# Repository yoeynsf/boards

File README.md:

# boards
A collection of the various boards that I make sometimes.

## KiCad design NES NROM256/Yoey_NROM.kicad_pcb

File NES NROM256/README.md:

# NES NROM-256
An open-source NES NROM cartridge PCB.

## License
This is licensed under the [TAPR Open Hardware License](www.tapr.org/OHL)

## Special Thanks 
- [@Trirosmos](https://github.com/Trirosmos)
- [@Lockster-inc](https://github.com/Lockster-Inc)

For advice and help!

- [@Persune](https://github.com/Gumball2415)

For supplying the cartridge pin footprint!

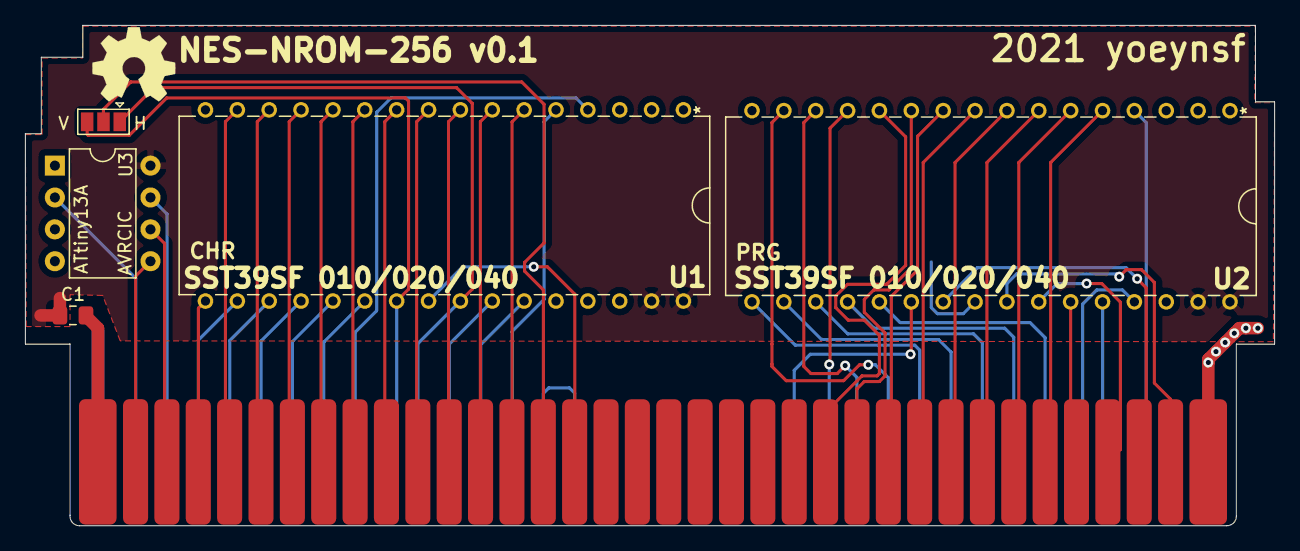
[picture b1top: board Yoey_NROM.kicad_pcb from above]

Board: 2 copper layers, 99.6 x 39.9 mm, 6 parts (0 on the bottom side), 55 nets.

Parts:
C1: 0.1µF; C_0805_2012Metric_Pad1.18x1.45mm_HandSolder
J1: Cart Connector; NES-CONN
JP1: V / H; SolderJumper-3_P1.3mm_Open_Pad1.0x1.5mm
U1: SST39SF 010/020/040; SST39SF040-70-4C-PHE
U2: SST39SF040; SST39SF040-70-4C-PHE
U3: CIC; DIP-8_W7.62mm

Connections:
CIC_+RST: J1.70, U3.7
CIC_CLK: J1.71, U3.2
CIC_to_NES: J1.35, U3.5
CIC_to_cart: J1.34, U3.6
CIRAM_A10: J1.22, JP1.2
CPU_A0: J1.13, U2.12
CPU_A1: J1.12, U2.11
CPU_A2: J1.11, U2.10
CPU_A3: J1.10, U2.9
CPU_A4: J1.9, U2.8
CPU_A5: J1.8, U2.7
CPU_A6: J1.7, U2.6
CPU_A7: J1.6, U2.5
CPU_A8: J1.5, U2.27
CPU_A9: J1.4, U2.26
CPU_A10: J1.3, U2.23
CPU_A11: J1.2, U2.25
CPU_A12: J1.39, U2.4
CPU_A13: J1.40, U2.28
CPU_A14: J1.41, U2.29
CPU_D0: J1.49, U2.13
CPU_D1: J1.48, U2.14
CPU_D2: J1.47, U2.15
CPU_D3: J1.46, U2.17
CPU_D4: J1.45, U2.18
CPU_D5: J1.44, U2.19
CPU_D6: J1.43, U2.20
CPU_D7: J1.42, U2.21
GND: J1.1, J1.72, U1.1, U1.2, U1.3, U1.16, U1.28, U1.29, U1.30, U2.1, U2.2, U2.3, U2.16, U2.24, U2.30, U3.4
unnamed: J1.57, J1.58
PPU_A0: J1.29, U1.12
PPU_A1: J1.28, U1.11
PPU_A2: J1.27, U1.10
PPU_A3: J1.26, U1.9
PPU_A4: J1.25, U1.8
PPU_A5: J1.24, U1.7
PPU_A6: J1.23, U1.6
PPU_A7: J1.59, U1.5
PPU_A8: J1.60, U1.27
PPU_A9: J1.61, U1.26
PPU_A10: J1.63, JP1.3, U1.23
PPU_A11: J1.62, JP1.1, U1.25
PPU_A12: J1.64, U1.4
PPU_A13: J1.65, U1.22
PPU_D0: J1.30, U1.13
PPU_D1: J1.31, U1.14
PPU_D2: J1.32, U1.15
PPU_D3: J1.33, U1.17
PPU_D4: J1.69, U1.18
PPU_D5: J1.68, U1.19
PPU_D6: J1.67, U1.20
PPU_D7: J1.66, U1.21
PPU_~RD: J1.21, U1.24
VCC: C1.1, C1.2, J1.36, U1.31, U1.32, U2.31, U2.32, U3.8
~ROMSEL: J1.50, U2.22

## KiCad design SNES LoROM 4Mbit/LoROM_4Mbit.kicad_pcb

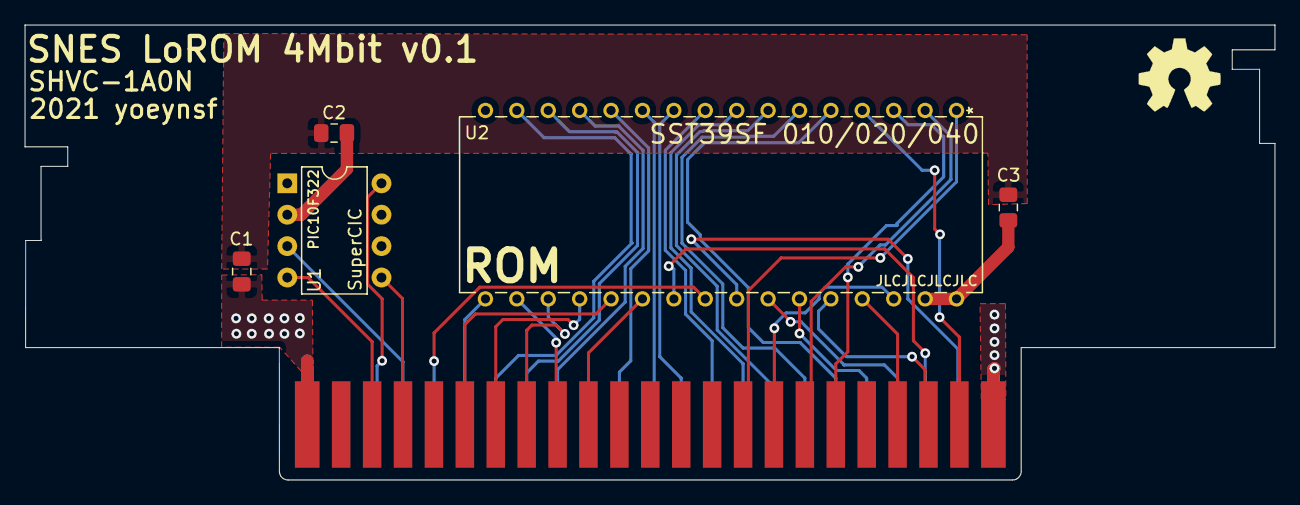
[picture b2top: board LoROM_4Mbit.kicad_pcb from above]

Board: 2 copper layers, 101.0 x 36.8 mm, 6 parts (0 on the bottom side), 37 nets.

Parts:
C1: 22uf; C_0805_2012Metric_Pad1.18x1.45mm_HandSolder
C2, C3: 0.1uf; C_0805_2012Metric_Pad1.18x1.45mm_HandSolder
J1: Cartridge Connector; SNES_Cart_pins
U1: PIC10F322; DIP-8_W7.62mm
U2: SST39SF 010/020/040; SST39SF040-70-4C-PHE

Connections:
/A0: J1.13, U2.12
/A1: J1.12, U2.11
/A2: J1.11, U2.10
/A3: J1.10, U2.9
/A4: J1.9, U2.8
/A5: J1.8, U2.7
/A6: J1.7, U2.6
/A7: J1.6, U2.5
/A8: J1.5, U2.27
/A9: J1.4, U2.26
/A10: J1.3, U2.23
/A11: J1.2, U2.25
/A12: J1.25, U2.4
/A13: J1.26, U2.28
/A14: J1.27, U2.29
/B0: J1.29, U2.3
/B1: J1.30, U2.2
/B2: J1.31, U2.30
/B3: J1.32, U2.1
/CIC_CLK: J1.44, U1.4
/CIC_DIN: J1.21, U1.8
/CIC_DOUT1: J1.20, U1.3
/CIC_DOUT2: J1.43, U1.5
/D0: J1.15, U2.13
/D1: J1.16, U2.14
/D2: J1.17, U2.15
/D3: J1.18, U2.17
/D4: J1.38, U2.18
/D5: J1.39, U2.19
/D6: J1.40, U2.20
/D7: J1.41, U2.21
/~CART: J1.37, U2.22
/~RD: J1.19, U2.24
GND: J1.1, J1.24, U1.7, U2.16
unnamed: C1.1, J1.23, J1.46
unnamed: C2.1, U1.2
VCC: C1.2, C2.2, C3.1, C3.2, U2.31, U2.32

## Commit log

2021-11-15 lorom
2021-11-15 upload
2021-11-16 logo

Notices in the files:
parts and their libraries:
Copyright 2021 Accelerated Designs. All rights reserved.
